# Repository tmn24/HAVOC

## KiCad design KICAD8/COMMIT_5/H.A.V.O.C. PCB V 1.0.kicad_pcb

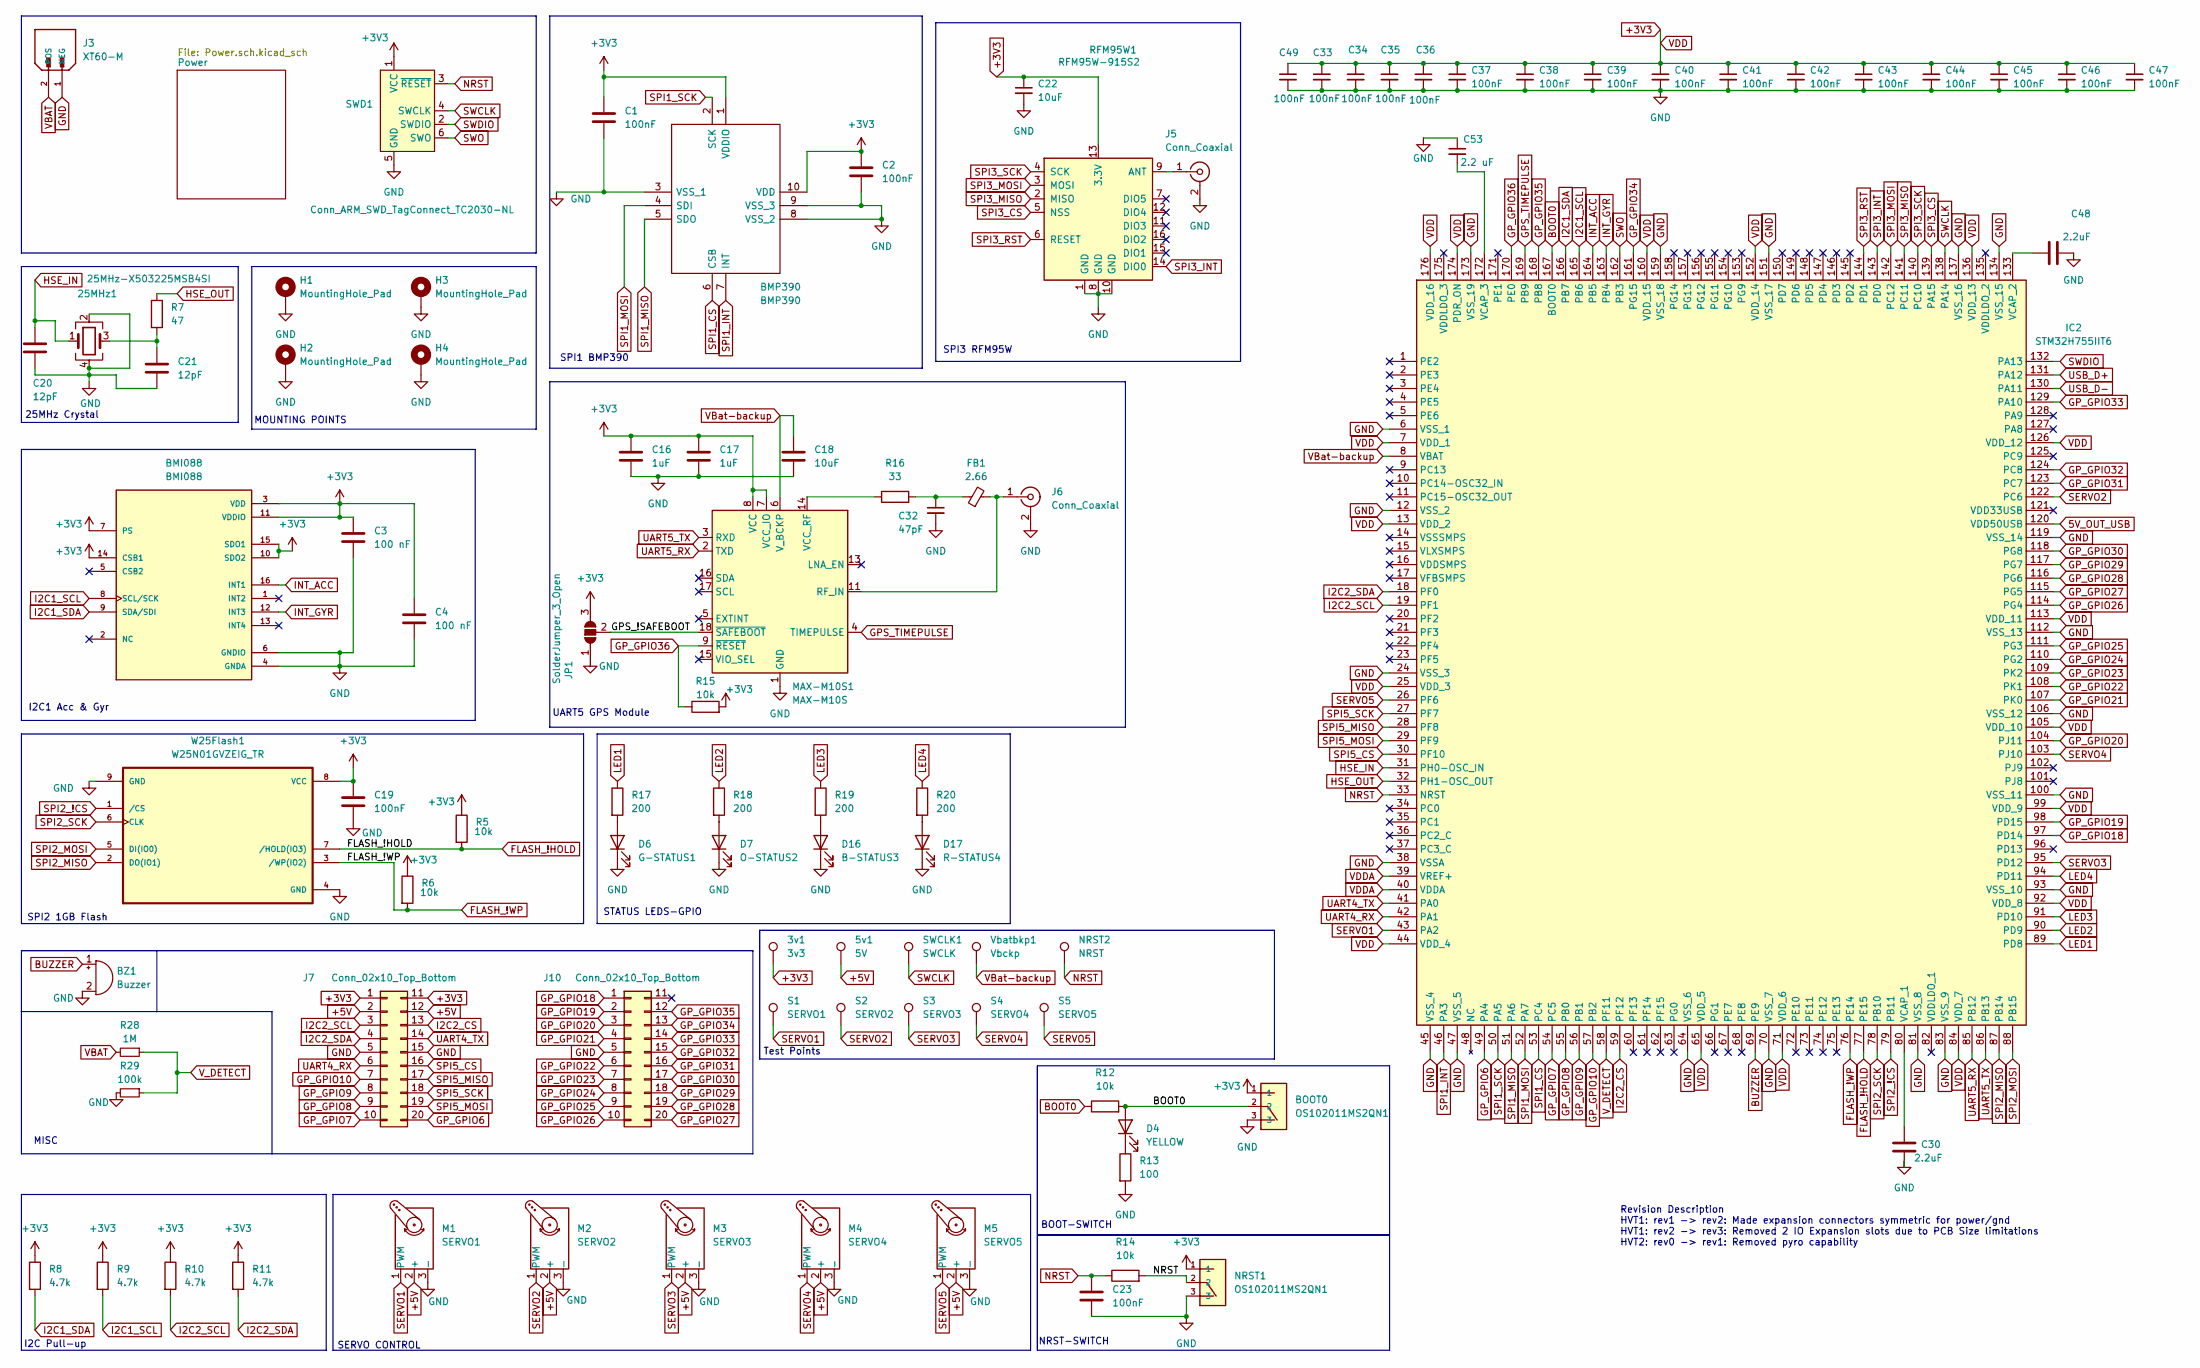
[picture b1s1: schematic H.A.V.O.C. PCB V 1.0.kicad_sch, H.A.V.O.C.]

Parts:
3v1: 3v3; TestPoint_Pad_1.5x1.5mm
5v1: 5V; TestPoint_Pad_1.5x1.5mm
25MHz1: 25MHz-X503225MSB4SI; Crystal_SMD_5032-4Pin_5.0x3.2mm
BMI088: BMI088; PQFN50P450X300X100-16N
BMP390: BMP390; 10LGA_2X2X0p75_BOS; Manufacturer_Part_Number BMP390; Mouser Part Number 262-BMP390
BOOT0: OS102011MS2QN1; SW_OS102011MS2QN1; DigiKey_Part_Number CKN9565-ND
BZ1: Buzzer; Buzzer_15x7.5RM7.6
C1, C2, C19, C23, C33, C34, C35, C36, C37, C38, C39, C40, C41, C42, C43, C44, C45, C46, C47, C49: 100nF; C_0805_2012Metric_Pad1.18x1.45mm_HandSolder
C3, C4: 100 nF; C_0805_2012Metric_Pad1.18x1.45mm_HandSolder
C16, C17: 1uF; C_0805_2012Metric_Pad1.18x1.45mm_HandSolder
C18, C22: 10uF; C_0805_2012Metric_Pad1.18x1.45mm_HandSolder
C20, C21: 12pF; C_0805_2012Metric_Pad1.18x1.45mm_HandSolder
C30, C48: 2.2uF; C_0805_2012Metric_Pad1.18x1.45mm_HandSolder
C32: 47pF; C_0805_2012Metric_Pad1.18x1.45mm_HandSolder
C53: 2.2 uF; C_0805_2012Metric_Pad1.18x1.45mm_HandSolder
D4: YELLOW; LED_0805_2012Metric_Pad1.15x1.40mm_HandSolder
D6: G-STATUS1; LED_0805_2012Metric_Pad1.15x1.40mm_HandSolder
D7: O-STATUS2; LED_0805_2012Metric_Pad1.15x1.40mm_HandSolder
D16: B-STATUS3; LED_0805_2012Metric_Pad1.15x1.40mm_HandSolder
D17: R-STATUS4; LED_0805_2012Metric_Pad1.15x1.40mm_HandSolder
FB1: 2.66; L_0805_2012Metric_Pad1.05x1.20mm_HandSolder
H1, H2, H3, H4: MountingHole_Pad; MountingHole_3mm_Pad
IC2: STM32H755IIT6; QFP50P2600X2600X160-176N; Manufacturer_Part_Number STM32H755IIT6; Mouser Part Number 511-STM32H755IIT6
J3: XT60-M; AMASS_XT60-M_1x02_P7.20mm_Vertical; PARTREV V1.2
J5, J6: Conn_Coaxial; SMA_Amphenol_901-143_Horizontal
J7, J10: Conn_02x10_Top_Bottom; PinSocket_2x10_P2.54mm_Vertical
JP1: SolderJumper_3_Open; SolderJumper-3_P1.3mm_Open_RoundedPad1.0x1.5mm_NumberLabels
M1: SERVO1; PinHeader_1x03_P2.54mm_Vertical
M2: SERVO2; PinHeader_1x03_P2.54mm_Vertical
M3: SERVO3; PinHeader_1x03_P2.54mm_Vertical
M4: SERVO4; PinHeader_1x03_P2.54mm_Vertical
M5: SERVO5; PinHeader_1x03_P2.54mm_Vertical
MAX-M10S1: MAX-M10S; ublox_MAX
NRST1: OS102011MS2QN1; SW_OS102011MS2QN1; DigiKey_Part_Number CKN9565-ND
NRST2: NRST; TestPoint_Pad_1.5x1.5mm
R5, R6, R12, R14, R15: 10k; R_0805_2012Metric_Pad1.20x1.40mm_HandSolder
R7: 47; R_0805_2012Metric_Pad1.20x1.40mm_HandSolder
R8, R9, R10, R11: 4.7k; R_0805_2012Metric_Pad1.20x1.40mm_HandSolder
R13: 100; R_0805_2012Metric_Pad1.20x1.40mm_HandSolder
R16: 33; R_0805_2012Metric_Pad1.20x1.40mm_HandSolder
R17, R18, R19, R20: 200; R_0805_2012Metric_Pad1.20x1.40mm_HandSolder
R28: 1M; R_0805_2012Metric_Pad1.20x1.40mm_HandSolder
R29: 100k; R_0805_2012Metric_Pad1.20x1.40mm_HandSolder
RFM95W1: RFM95W-915S2; HOPERF_RFM9XW_SMD
S1: SERVO1; TestPoint_Pad_1.5x1.5mm
S2: SERVO2; TestPoint_Pad_1.5x1.5mm
S3: SERVO3; TestPoint_Pad_1.5x1.5mm
S4: SERVO4; TestPoint_Pad_1.5x1.5mm
S5: SERVO5; TestPoint_Pad_1.5x1.5mm
SWCLK1: SWCLK; TestPoint_Pad_1.5x1.5mm
SWD1: Conn_ARM_SWD_TagConnect_TC2030-NL; Tag-Connect_TC2030-IDC-NL_2x03_P1.27mm_Vertical
Vbatbkp1: Vbckp; TestPoint_Pad_1.5x1.5mm
W25Flash1: W25N01GVZEIG_TR; SON127P800X600X80-9N

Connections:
5V_OUT_USB: IC2.120 (VDD50USB); also elsewhere on the board
+3V3: 3v1.1, BMI088.3 (VDD), BMI088.7 (PS), BMI088.10 (SDO2), BMI088.11 (VDDIO), BMI088.14 (CSB1), BMI088.15 (SDO1), BMP390.1 (VDDIO), BMP390.10 (VDD), BOOT0.1, C1.2, C2.1, C3.1, C4.1, C16.1, C17.1, C19.1, C22.1, C33.1, C34.1, C35.1, C36.1, C37.1, C38.1, C39.1, C40.1, C41.1, C42.1, C43.1, C44.1, C45.1, C46.1, C47.1, C49.1, IC2.7 (VDD_1), IC2.13 (VDD_2), IC2.25 (VDD_3), IC2.44 (VDD_4), IC2.65 (VDD_5), IC2.71 (VDD_6), IC2.84 (VDD_7), IC2.92 (VDD_8), IC2.99 (VDD_9), IC2.105 (VDD_10), IC2.113 (VDD_11), IC2.126 (VDD_12), IC2.136 (VDD_13), IC2.152 (VDD_14), IC2.160 (VDD_15), IC2.174 (PDR_ON), IC2.176 (VDD_16), J7.1, J7.11, JP1.3 (B), MAX-M10S1.7 (VCC_IO), MAX-M10S1.8 (VCC), NRST1.1, R5.1, R6.1, R8.1, R9.1, R10.1, R11.1, R15.2, RFM95W1.13 (3.3V), SWD1.1 (VCC), W25Flash1.8 (VCC); also elsewhere on the board
+5V: 5v1.1, J7.2, J7.12, M1.2 (+), M2.2 (+), M3.2 (+), M4.2 (+), M5.2 (+); also elsewhere on the board
/GPS_!SAFEBOOT: JP1.2 (C), MAX-M10S1.18 (~SAFEBOOT)
BOOT0: BOOT0.2, D4.2 (A), IC2.167 (BOOT0), R12.1, R12.2
BUZZER: BZ1.1 (+), IC2.69 (PE9)
FLASH_!HOLD: IC2.77 (PE15), R5.2, W25Flash1.7 (/HOLD(IO3))
FLASH_!WP: IC2.76 (PE14), R6.2, W25Flash1.3 (/WP(IO2))
GND: 25MHz1.2, 25MHz1.4, BMI088.4 (GNDA), BMI088.6 (GNDIO), BMP390.3 (VSS_1), BMP390.8 (VSS_2), BMP390.9 (VSS_3), BOOT0.3, BZ1.2 (-), C1.1, C2.2, C3.2, C4.2, C16.2, C17.2, C18.2, C19.2, C20.2, C21.2, C22.2, C23.2, C30.2, C32.2, C33.2, C34.2, C35.2, C36.2, C37.2, C38.2, C39.2, C40.2, C41.2, C42.2, C43.2, C44.2, C45.2, C46.2, C47.2, C48.2, C49.2, C53.1, D6.1 (K), D7.1 (K), D16.1 (K), D17.1 (K), H1.1, H2.1, H3.1, H4.1, IC2.6 (VSS_1), IC2.12 (VSS_2), IC2.24 (VSS_3), IC2.38 (VSSA), IC2.45 (VSS_4), IC2.47 (VSS_5), IC2.64 (VSS_6), IC2.70 (VSS_7), IC2.81 (VSS_8), IC2.83 (VSS_9), IC2.93 (VSS_10), IC2.100 (VSS_11), IC2.106 (VSS_12), IC2.112 (VSS_13), IC2.119 (VSS_14), IC2.134 (VSS_15), IC2.137 (VSS_16), IC2.151 (VSS_17), IC2.159 (VSS_18), IC2.173 (VSS_19), J3.1 (NEG), J5.2 (Ext), J6.2 (Ext), J7.5, J7.15, J10.5, JP1.1 (A), M1.3 (-), M2.3 (-), M3.3 (-), M4.3 (-), M5.3 (-), MAX-M10S1.1 (GND), MAX-M10S1.10 (GND), MAX-M10S1.12 (GND), NRST1.3, R13.2, R29.2, RFM95W1.1 (GND), RFM95W1.8 (GND), RFM95W1.10 (GND), SWD1.5 (GND), W25Flash1.4 (GND), W25Flash1.9 (GND); also elsewhere on the board
GPS_TIMEPULSE: IC2.169 (PB9), MAX-M10S1.4 (TIMEPULSE)
GP_GPIO6: IC2.49 (PA4), J7.20
GP_GPIO7: IC2.54 (PC5), J7.10
GP_GPIO8: IC2.55 (PB0), J7.9
GP_GPIO9: IC2.56 (PB1), J7.8
GP_GPIO10: IC2.57 (PB2), J7.7
GP_GPIO18: IC2.97 (PD14), J10.1
GP_GPIO19: IC2.98 (PD15), J10.2
GP_GPIO20: IC2.104 (PJ11), J10.3
GP_GPIO21: IC2.107 (PK0), J10.4
GP_GPIO22: IC2.108 (PK1), J10.6
GP_GPIO23: IC2.109 (PK2), J10.7
GP_GPIO24: IC2.110 (PG2), J10.8
GP_GPIO25: IC2.111 (PG3), J10.9
GP_GPIO26: IC2.114 (PG4), J10.10
GP_GPIO27: IC2.115 (PG5), J10.20
GP_GPIO28: IC2.116 (PG6), J10.19
GP_GPIO29: IC2.117 (PG7), J10.18
GP_GPIO30: IC2.118 (PG8), J10.17
GP_GPIO31: IC2.123 (PC7), J10.16
GP_GPIO32: IC2.124 (PC8), J10.15
GP_GPIO33: IC2.129 (PA10), J10.14
GP_GPIO34: IC2.161 (PG15), J10.13
GP_GPIO35: IC2.168 (PB8), J10.12
GP_GPIO36: IC2.170 (PE0), MAX-M10S1.9 (~RESET), R15.1
HSE_IN: 25MHz1.1, C20.1, IC2.31 (PH0-OSC_IN)
HSE_OUT: IC2.32 (PH1-OSC_OUT), R7.1
I2C1_SCL: BMI088.8 (SCL/SCK), IC2.165 (PB6), R9.2
I2C1_SDA: BMI088.9 (SDA/SDI), IC2.166 (PB7), R8.2
I2C2_CS: IC2.59 (PF12), J7.13
I2C2_SCL: IC2.19 (PF1), J7.3, R10.2
I2C2_SDA: IC2.18 (PF0), J7.4, R11.2
INT_ACC: BMI088.16 (INT1), IC2.164 (PB5)
INT_GYR: BMI088.12 (INT3), IC2.163 (PB4)
LED1: IC2.89 (PD8), R17.1
LED2: IC2.90 (PD9), R18.1
LED3: IC2.91 (PD10), R19.1
LED4: IC2.94 (PD11), R20.1
NRST: C23.1, IC2.33 (NRST), NRST1.2, NRST2.1, R14.1, R14.2, SWD1.3 (~RESET)
unnamed: 25MHz1.3, C21.1, R7.2
unnamed: C32.1, FB1.1, R16.2
unnamed: D4.1 (K), R13.1
unnamed: D6.2 (A), R17.2
unnamed: D7.2 (A), R18.2
unnamed: D16.2 (A), R19.2
unnamed: D17.2 (A), R20.2
unnamed: C30.1, IC2.80 (VCAP_1)
unnamed: C48.1, IC2.133 (VCAP_2)
unnamed: C53.2, IC2.172 (VCAP_3)
unnamed: J5.1 (In), RFM95W1.9 (ANT)
unnamed: FB1.2, J6.1 (In), MAX-M10S1.11 (RF_IN)
unnamed: MAX-M10S1.14 (VCC_RF), R16.1
SERVO1: IC2.43 (PA2), M1.1 (PWM), S1.1
SERVO2: IC2.122 (PC6), M2.1 (PWM), S2.1
SERVO3: IC2.95 (PD12), M3.1 (PWM), S3.1
SERVO4: IC2.103 (PJ10), M4.1 (PWM), S4.1
SERVO5: IC2.26 (PF6), M5.1 (PWM), S5.1
SPI1_CS: BMP390.6 (CSB), IC2.53 (PC4)
SPI1_INT: BMP390.7 (INT), IC2.46 (PA3)
SPI1_MISO: BMP390.5 (SDO), IC2.51 (PA6)
SPI1_MOSI: BMP390.4 (SDI), IC2.52 (PA7)
SPI1_SCK: BMP390.2 (SCK), IC2.50 (PA5)
SPI2_!CS: IC2.79 (PB11), W25Flash1.1 (/CS)
SPI2_MISO: IC2.87 (PB14), W25Flash1.2 (DO(IO1))
SPI2_MOSI: IC2.88 (PB15), W25Flash1.5 (DI(IO0))
SPI2_SCK: IC2.78 (PB10), W25Flash1.6 (CLK)
SPI3_CS: IC2.139 (PA15), RFM95W1.5 (NSS)
SPI3_INT: IC2.143 (PD0), RFM95W1.14 (DIO0)
SPI3_MISO: IC2.141 (PC11), RFM95W1.2 (MISO)
SPI3_MOSI: IC2.142 (PC12), RFM95W1.3 (MOSI)
SPI3_RST: IC2.144 (PD1), RFM95W1.6 (RESET)
SPI3_SCK: IC2.140 (PC10), RFM95W1.4 (SCK)
SPI5_CS: IC2.30 (PF10), J7.16
SPI5_MISO: IC2.28 (PF8), J7.17
SPI5_MOSI: IC2.29 (PF9), J7.19
SPI5_SCK: IC2.27 (PF7), J7.18
SWCLK: IC2.138 (PA14), SWCLK1.1, SWD1.4 (SWCLK)
SWDIO: IC2.132 (PA13), SWD1.2 (SWDIO)
SWO: IC2.162 (PB3), SWD1.6 (SWO)
UART4_RX: IC2.42 (PA1), J7.6
UART4_TX: IC2.41 (PA0), J7.14
UART5_RX: IC2.85 (PB12), MAX-M10S1.2 (TXD)
UART5_TX: IC2.86 (PB13), MAX-M10S1.3 (RXD)
USB_D+: IC2.131 (PA12); also elsewhere on the board
USB_D-: IC2.130 (PA11); also elsewhere on the board
VBAT: J3.2 (POS), R28.2; also elsewhere on the board
VBat-backup: C18.1, IC2.8 (VBAT), MAX-M10S1.6 (V_BCKP), Vbatbkp1.1; also elsewhere on the board
VDDA: IC2.39 (VREF+), IC2.40 (VDDA); also elsewhere on the board
V_DETECT: IC2.58 (PF11), R28.1, R29.1

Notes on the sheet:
SPI1 BMP390
Revision Description HVT1: rev1 -> rev2: Made expansion connectors symmetric for power/gnd HVT1: rev2 -> rev3: Removed 2 IO Expansion slots due to PCB Size limitations HVT2: rev0 -> rev1: Removed pyro capability
Test Points
I2C1 Acc & Gyr
SPI2 1GB Flash
SERVO CONTROL
NRST-SWITCH
SPI3 RFM95W
UART5 GPS Module
BOOT-SWITCH
I2C Pull-up
25MHz Crystal
MISC
MOUNTING POINTS
STATUS LEDS-GPIO

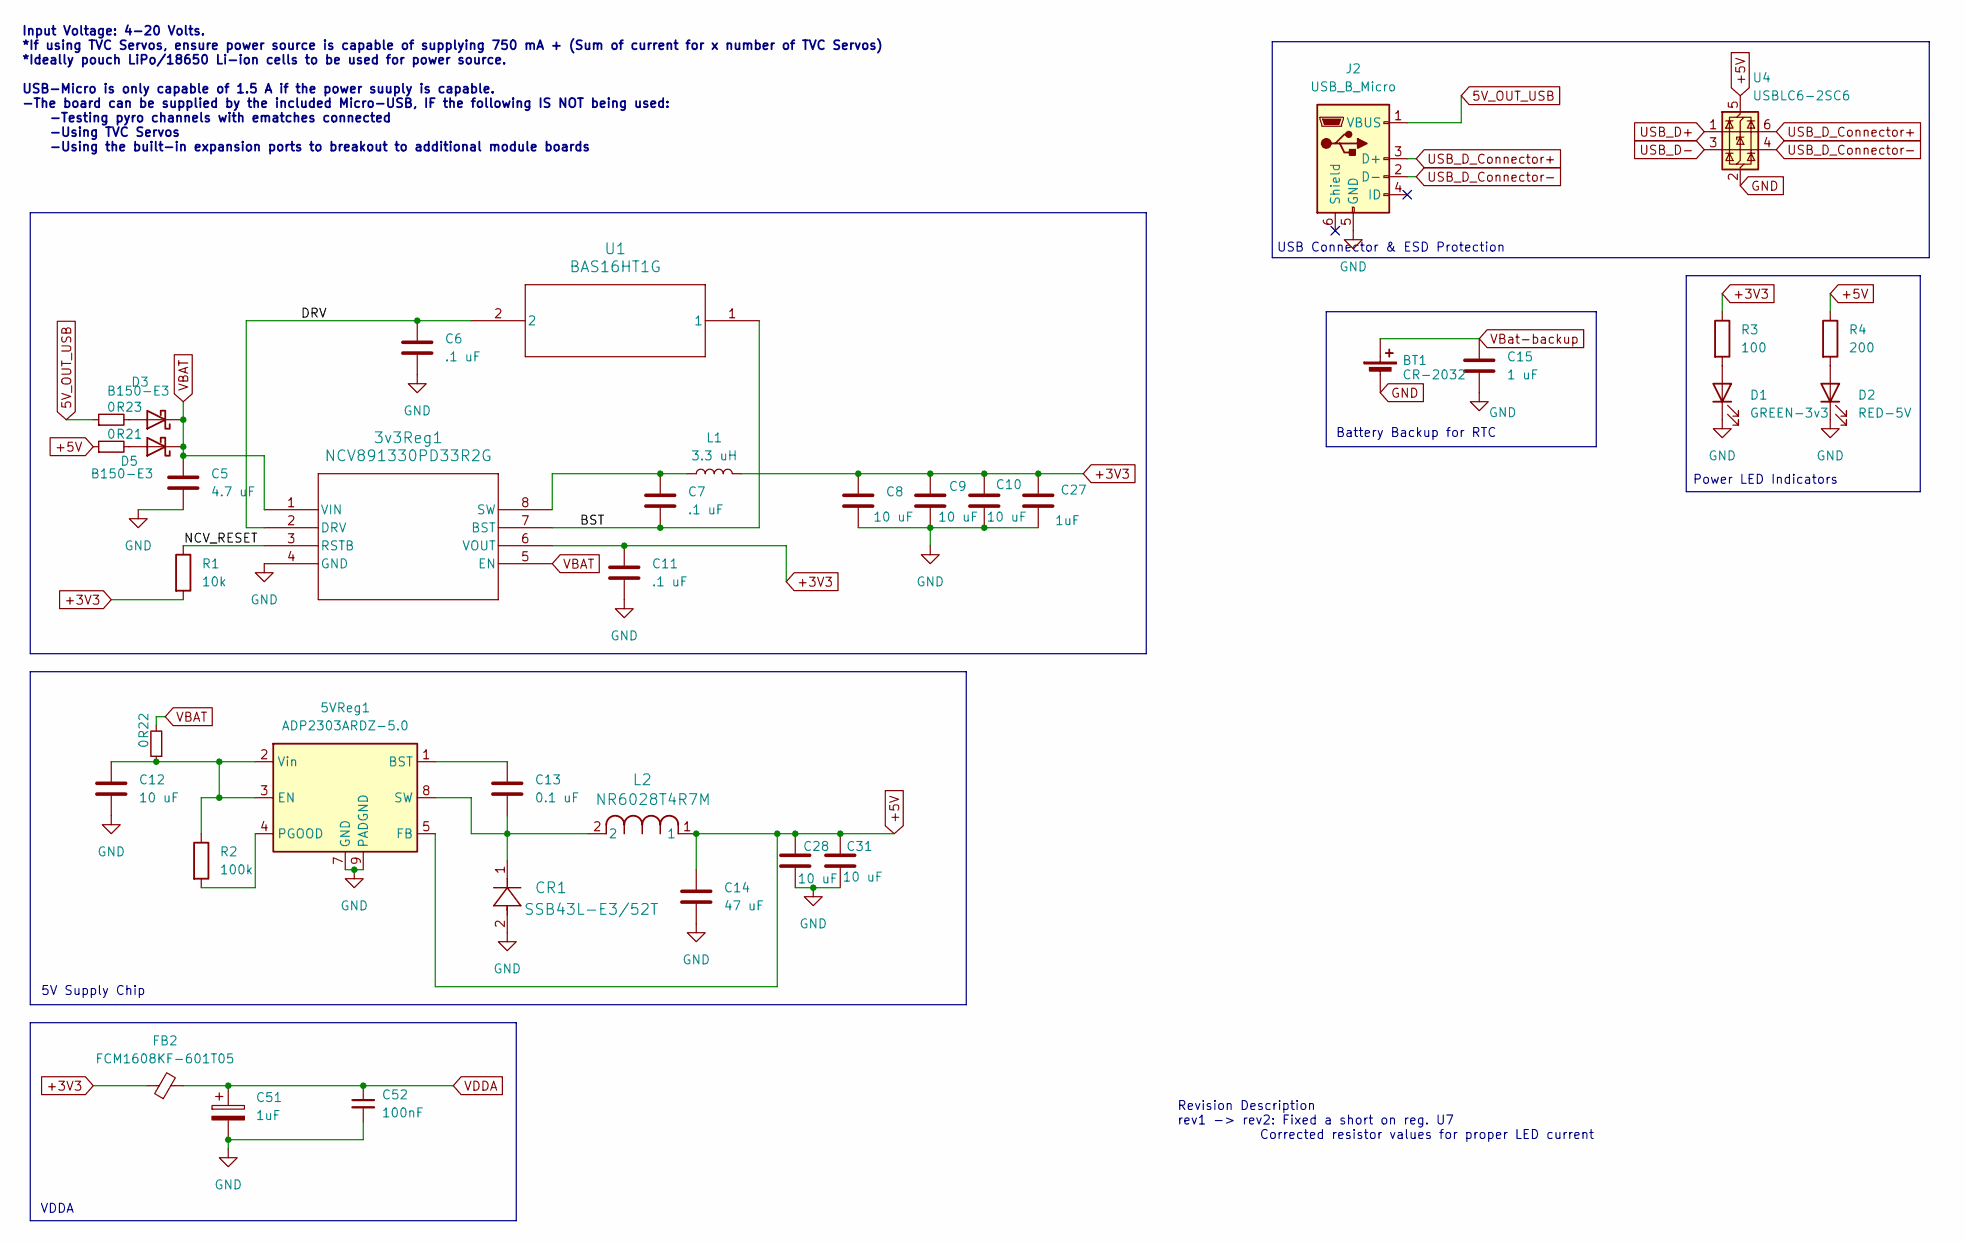
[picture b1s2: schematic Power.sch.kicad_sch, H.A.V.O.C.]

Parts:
3v3Reg1: NCV891330PD33R2G; SOIC8_3P9X4P9_ONS
5VReg1: ADP2303ARDZ-5.0; SOIC-8-1EP_3.9x4.9mm_P1.27mm_EP2.29x3mm
BT1: CR-2032; cr 2032 holder
C5: 4.7 uF; C_0805_2012Metric_Pad1.18x1.45mm_HandSolder
C6, C7, C11: .1 uF; C_0805_2012Metric_Pad1.18x1.45mm_HandSolder
C8, C9, C10, C12, C28, C31: 10 uF; C_0805_2012Metric_Pad1.18x1.45mm_HandSolder
C13: 0.1 uF; C_0805_2012Metric_Pad1.18x1.45mm_HandSolder
C14: 47 uF; C_0805_2012Metric_Pad1.18x1.45mm_HandSolder
C15: 1 uF; C_0805_2012Metric_Pad1.18x1.45mm_HandSolder
C27: 1uF; C_0805_2012Metric_Pad1.18x1.45mm_HandSolder
C51: 1uF; CP_Elec_4x5.4
C52: 100nF; C_0805_2012Metric_Pad1.18x1.45mm_HandSolder
CR1: SSB43L-E3/52T; DIODE_DO214AA_MBRS
D1: GREEN-3v3; LED_0805_2012Metric_Pad1.15x1.40mm_HandSolder
D2: RED-5V; LED_0805_2012Metric_Pad1.15x1.40mm_HandSolder
D3, D5: B150-E3; D_SMA
FB2: FCM1608KF-601T05; L_0603_1608Metric
J2: USB_B_Micro; USB_Micro-B_Wuerth_629105150521
L1: 3.3 uH; IND_NRS5030_TAY
L2: NR6028T4R7M; IND_NR6028T4R7M
R1: 10k; R_0805_2012Metric_Pad1.20x1.40mm_HandSolder
R2: 100k; R_0805_2012Metric_Pad1.20x1.40mm_HandSolder
R3: 100; R_0805_2012Metric_Pad1.20x1.40mm_HandSolder
R4: 200; R_0805_2012Metric_Pad1.20x1.40mm_HandSolder
R21, R22, R23: 0; R_0805_2012Metric_Pad1.20x1.40mm_HandSolder
U1: BAS16HT1G; SOD_16HT1G_ONS
U4: USBLC6-2SC6; SOT-23-6

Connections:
5V_OUT_USB: J2.1 (VBUS), R23.1; also elsewhere on the board
+3V3: 3v3Reg1.6 (VOUT), C8.1, C9.1, C10.1, C11.1, C27.1, FB2.1, L1.2, R1.2, R3.1; also elsewhere on the board
+5V: 5VReg1.5 (FB), C14.1, C28.1, C31.1, L2.1, R4.1, R21.1, U4.5 (VBUS); also elsewhere on the board
/Power/BST: 3v3Reg1.7 (BST), C7.2, U1.1
/Power/DRV: 3v3Reg1.2 (DRV), C6.1, U1.2
/Power/NCV_RESET: 3v3Reg1.3 (RSTB), R1.1
GND: 3v3Reg1.4 (GND), 5VReg1.7 (GND), 5VReg1.9 (PADGND), BT1.2 (-), C5.2, C6.2, C8.2, C9.2, C10.2, C11.2, C12.2, C14.2, C15.2, C27.2, C28.2, C31.2, C51.2, C52.2, CR1.2, D1.1 (K), D2.1 (K), J2.5 (GND), U4.2 (GND); also elsewhere on the board
unnamed: 3v3Reg1.8 (SW), C7.1, L1.1
unnamed: 5VReg1.1 (BST), C13.1
unnamed: 5VReg1.2 (Vin), 5VReg1.3 (EN), C12.1, R2.1, R22.1
unnamed: 5VReg1.4 (PGOOD), R2.2
unnamed: 5VReg1.8 (SW), C13.2, CR1.1, L2.2
unnamed: D1.2 (A), R3.2
unnamed: D2.2 (A), R4.2
unnamed: D3.2 (A), R23.2
unnamed: D5.2 (A), R21.2
USB_D+: U4.1 (I/O1); also elsewhere on the board
USB_D-: U4.3 (I/O2); also elsewhere on the board
USB_D_Connector+: J2.3 (D+), U4.6 (I/O1)
USB_D_Connector-: J2.2 (D-), U4.4 (I/O2)
VBAT: 3v3Reg1.1 (VIN), 3v3Reg1.5 (EN), C5.1, D3.1 (K), D5.1 (K), R22.2; also elsewhere on the board
VBat-backup: BT1.1 (+), C15.1; also elsewhere on the board
VDDA: C51.1, C52.1, FB2.2; also elsewhere on the board

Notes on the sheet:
USB Connector & ESD Protection
5V Supply Chip
Input Voltage: 4-20 Volts. *If using TVC Servos, ensure power source is capable of supplying 750 mA + (Sum of current for x number of TVC Servos) *Ideally pouch LiPo/18650 Li-ion cells to be used for power source. USB-Micro is only capable of 1.5 A if the power suuply is capable. -The board can be 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
Revision Description rev1 -> rev2: Fixed a short on reg. U7 Corrected resistor values for proper LED current
VDDA
Power LED Indicators
Battery Backup for RTC

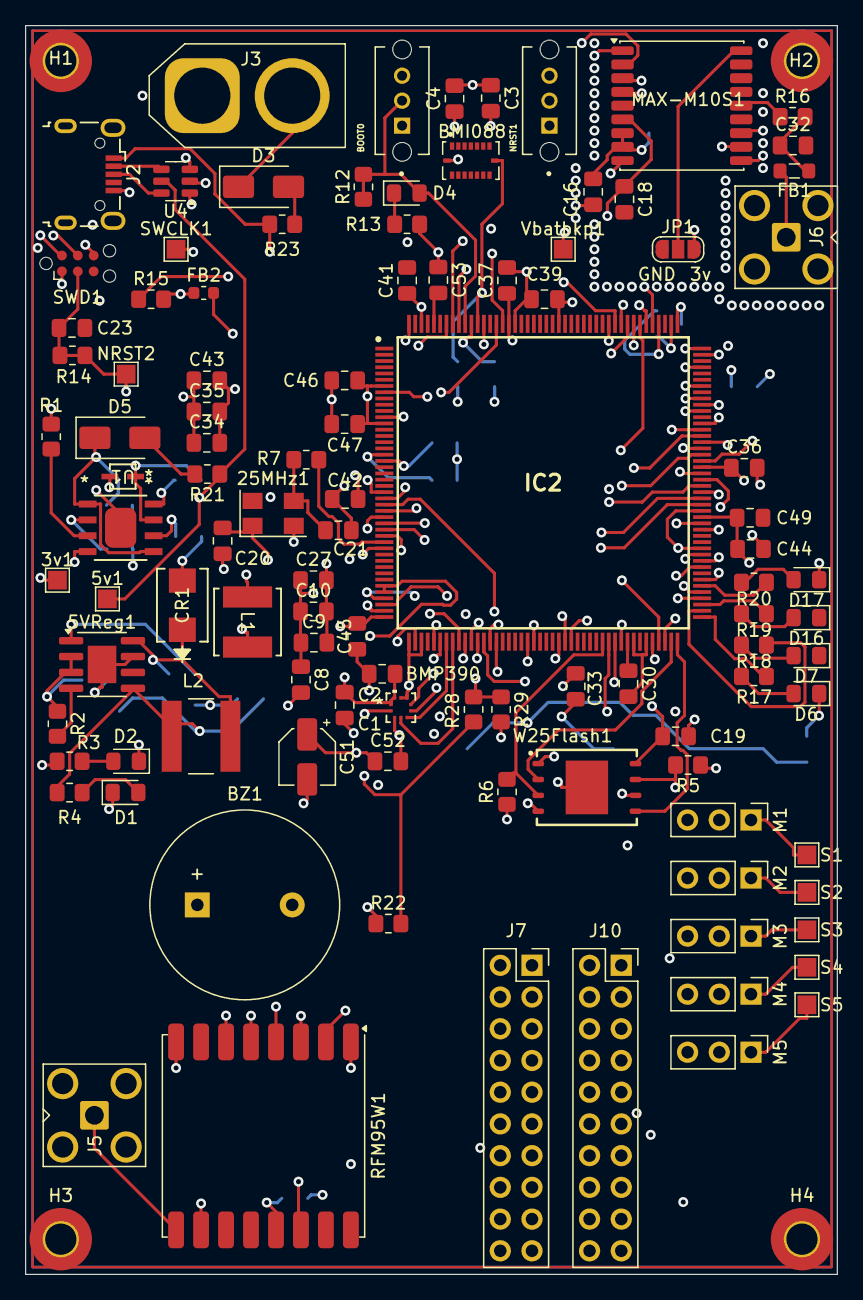
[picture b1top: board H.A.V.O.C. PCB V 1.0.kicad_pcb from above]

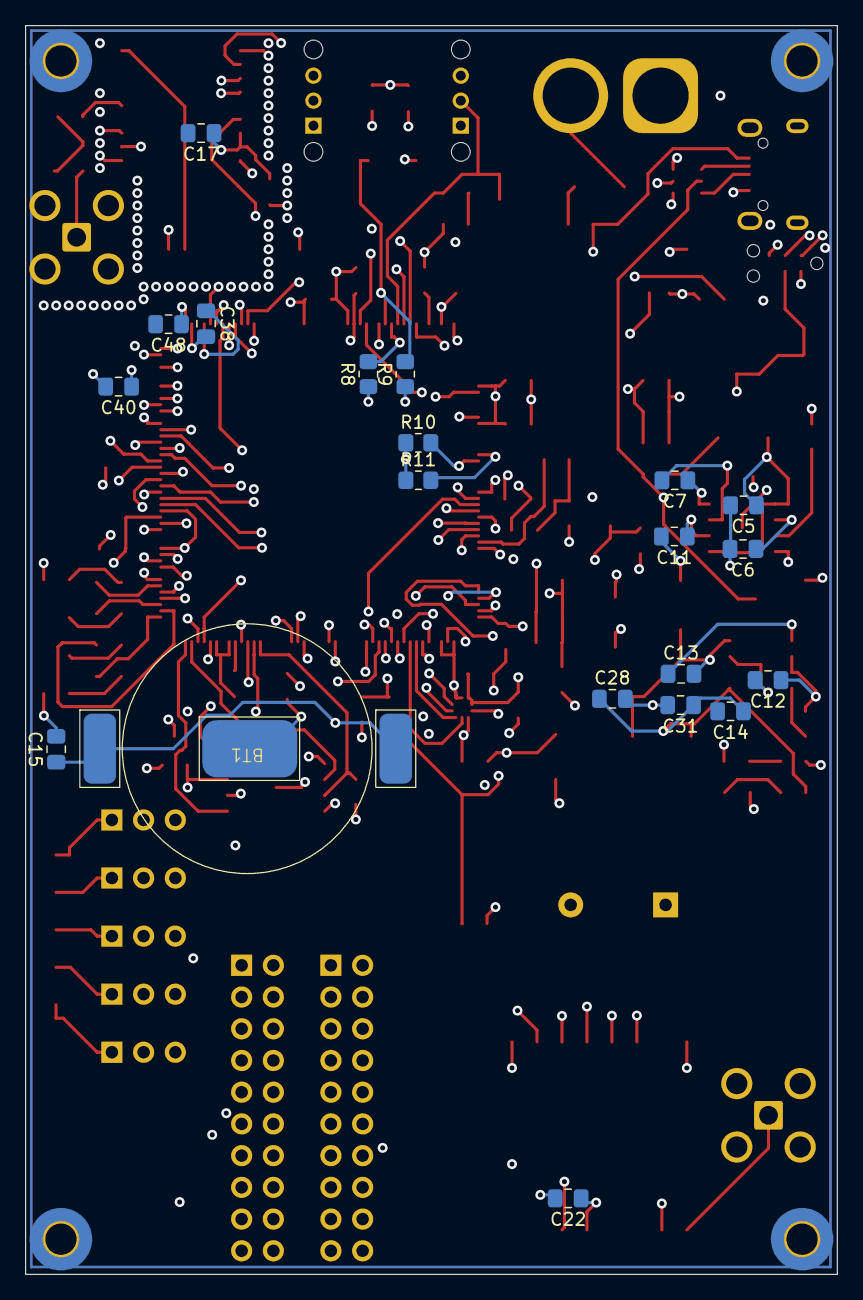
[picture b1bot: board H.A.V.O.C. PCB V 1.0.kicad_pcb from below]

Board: 8 copper layers, 65.0 x 100.0 mm, 129 parts (20 on the bottom side), 112 nets.

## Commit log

2024-07-11 Create LICENSE
2024-07-11 Reorganization of Files
    Organized files
2024-07-16 Rev2-Annotations & Schematic
    *Added annotations for certain components/systems based on feedback.
    *Added data sheets for most (if not all) chips used
    *Corrected resistor values around LEDs for proper current flow
    *Fixed a short on regulator U7 caused by moving that section of schematic
    *Created an archival system to retain easy access to older hardware designs
2024-08-04 Physical Hardware Design
    *Created the first iteration of the PCB
    *Created 3D model of V1.0.0
    *Created PDF of individual layer views
    *Revised primary schematic page: Removed 2/4 breakout connectors due to lack of need for current design
    *Removed connections for NC pins
2024-08-05 Revision 4-Adjusting traces
    Adjusted traces to provide more spacing, received feedback to go to 8 layer pcb pending review from other sources.
2024-08-28 Changes to V1 PCB before ordering
    Stitching vias for gnd planes, change to 8 layer board
2024-10-21 In-progress Changes
    HVT 1 -> 2, switching to a different format without pyro system. In between development, issues with HVT 1 from manufacturer, one from my design.
2024-10-24 Intermediary Progress on HVT2
    Removed pyro circuits for cost reasons, most of layout completed, traces need to be routed still
2024-10-29 HVT2-No Traces
    HVT2 layout complete, no traces yet
2024-10-31 Changes to gnd planes
    Modified gnd planes- bckp before routing/scripting
2024-11-05 Routed Traces-Preliminary
    Notes:
    -Differential pair is NOT routed yet
    -Need to evaluate for shorts in traces/design rules
2024-11-07 Test commit UART4_TX
